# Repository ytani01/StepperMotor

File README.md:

# Stepper Motor Class for Raspberry Pi, Python3 and pigpio

ステッピングモーター(stepper motor) Python3ライブラリ

## StepMtrTh class

* マルチスレッド版
* 回転中でも制御可能。

## StepMtr class

* シングルスレッド版
* 指定されたカウントまでブロックし、他の操作ができない。

## 動作環境

* 本体: Raspberry Pi
* モータードライバー: DRV8835, ULN2003
* ステッピングモーター: 28BYJ-48-5V
* プログラミング言語: Python3
* GPIO制御ライブラリ: pigpio

## 0. TL;DR

Install
```bash
$ cd ~
$ python3 -m venv env1
$ cd env1
$ . ./bin/activate

(env1)$ git clone https://github.com/ytani01/StepperMotor.git
(env1)$ cd StepperMotor

(env1)$ pip install -U pip setuptools wheel
(env1)$ hash -r
(env1)$ pip install .
```

Run test program
```bash
(env1)$ sudo pigpiod
(env1)$ python -m stepmtr PIN1 PIN2 PIN3 PIN4
```

Sample program
[sample.py](sample.py)

## 1. Hardware

### 1.1 Raspberry Pi + DRV8835 + 28BYJ-48-5V

配線と、引数の順番の違いに注意！

### 1.2 ULN2003モジュールの場合

```
AIN1 -> IN1
AIN2 -> IN2
BIN1 -> IN3
BIN2 -> IN4
```

## 2. API

```bash
$ python3 -m pydoc stepmtr
```

## 3. Software Architecture

呼び出し階層
```
 -----------------
| StepMtrTh class |
|-----------------|
|  StepMtr class  |
|-----------------|
|  pigpio class   |
 -----------------
```

## A. Links

* [DRV8835](https://akizukidenshi.com/catalog/g/gK-09848/)
* [28BYJ-48-5V and ULN2003 5個セット](https://www.amazon.co.jp/gp/product/B010RYH74U/)
* [pygpio -- Python Interface](http://abyz.me.uk/rpi/pigpio/python.html)

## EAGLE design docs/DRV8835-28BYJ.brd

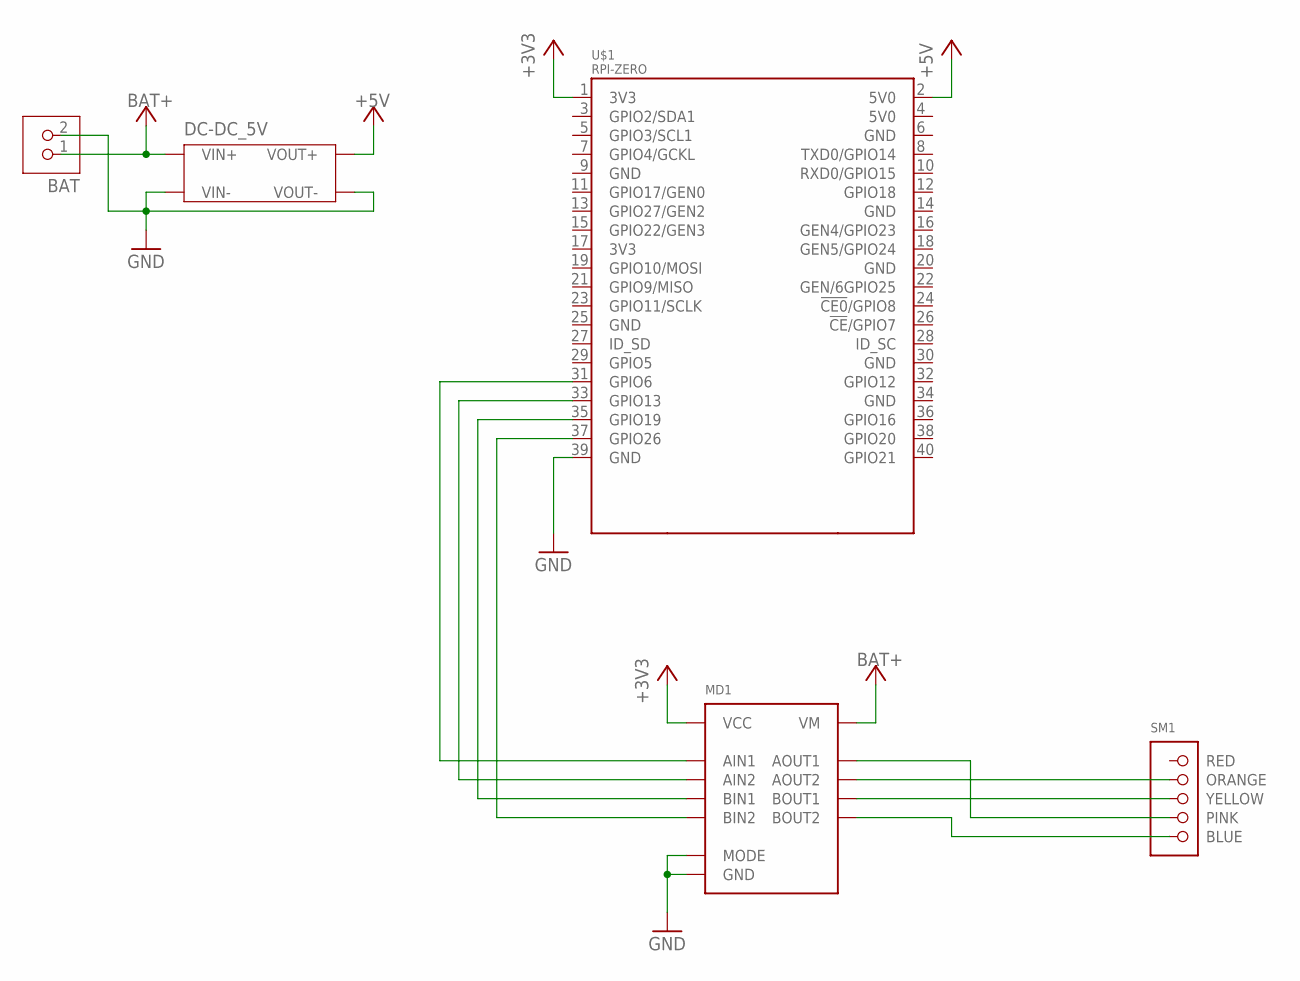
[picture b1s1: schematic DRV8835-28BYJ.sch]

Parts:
BAT: JST-PH2
DC-DC_5V: DCDC-5V_28V-2A
MD1: DRV8835MOD
SM1: 28BYJ-48-5V
U$1: RPI-ZERO; RASPBERRYPI_BASTELSTUBE_V13_RASPI_BOARD_B+_FULL

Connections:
+3V3: MD1.VCC, U$1.1 (3V3)
+5V: DC-DC_5V.VOUT+, U$1.2 (5V0)
BAT+: BAT.1, DC-DC_5V.VIN+, MD1.VM
BLUE: MD1.BOUT2, SM1.BLUE
GND: BAT.2, DC-DC_5V.VIN-, DC-DC_5V.VOUT-, MD1.GND, MD1.MODE, U$1.39 (GND)
GPIO6: MD1.AIN1, U$1.31 (GPIO6)
GPIO13: MD1.AIN2, U$1.33 (GPIO13)
GPIO19: MD1.BIN1, U$1.35 (GPIO19)
GPIO26: MD1.BIN2, U$1.37 (GPIO26)
ORANGE: MD1.AOUT2, SM1.ORANGE
PINK: MD1.AOUT1, SM1.PINK
YELLOW: MD1.BOUT1, SM1.YELLOW

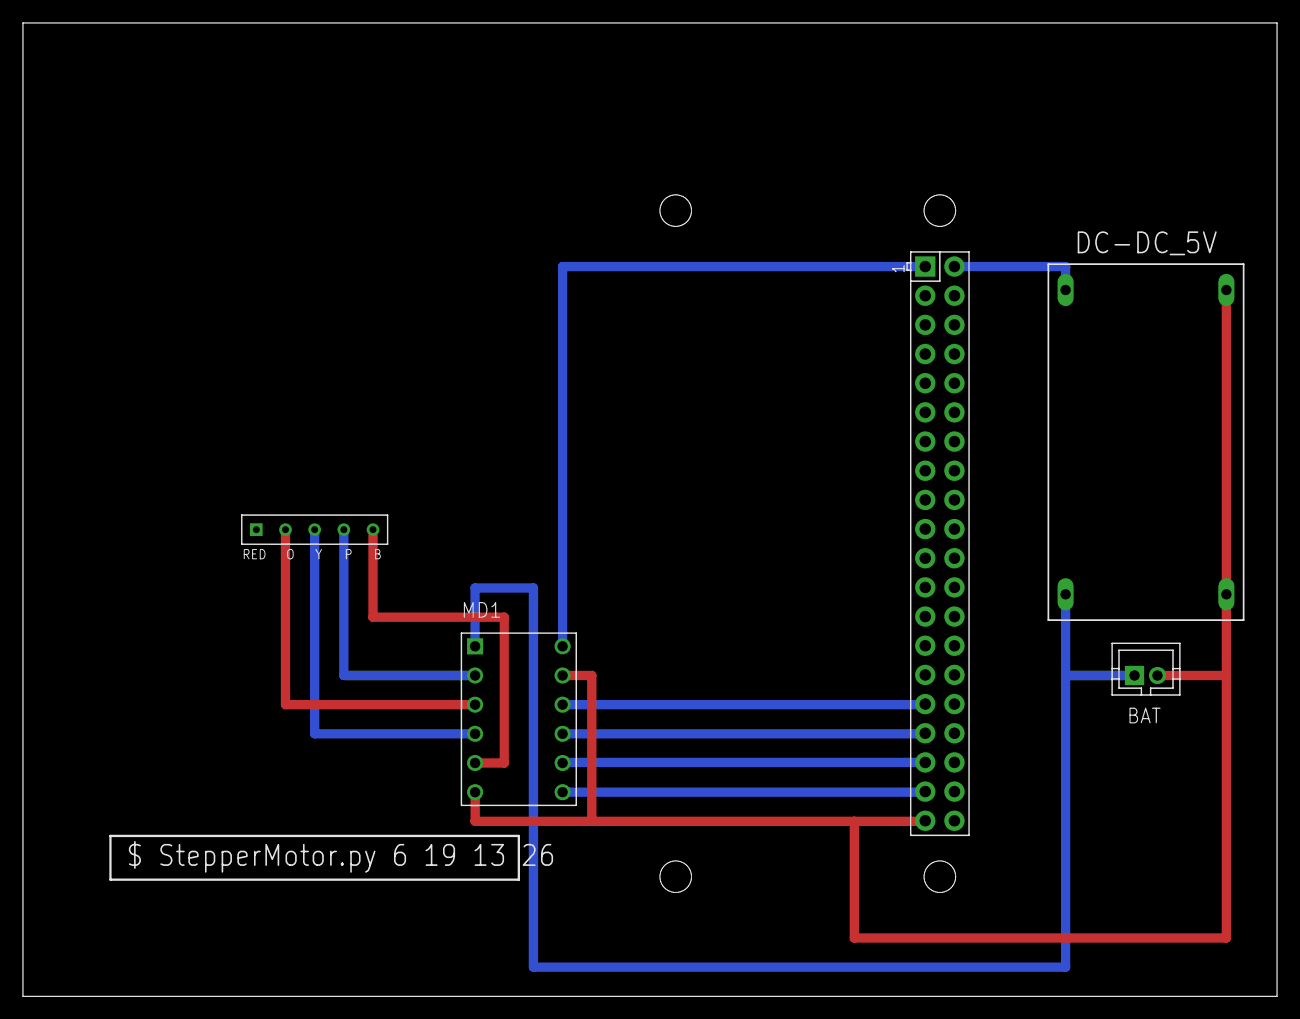
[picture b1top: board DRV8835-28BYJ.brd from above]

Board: 2 copper layers, 109.2 x 84.8 mm, 5 parts (0 on the bottom side), 12 nets.

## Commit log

2020-12-01 add ULN2003
2020-12-01 StepMtrTh
2020-12-17 [del] MusicBoxRotationMotor.py (move to MusicBox/)
2020-12-17 [update] README.md
2021-01-03 [rename] ``doc/`` to ``docs/``
2021-01-03 [update] stepmtr
2021-01-03 [fix] README.md
